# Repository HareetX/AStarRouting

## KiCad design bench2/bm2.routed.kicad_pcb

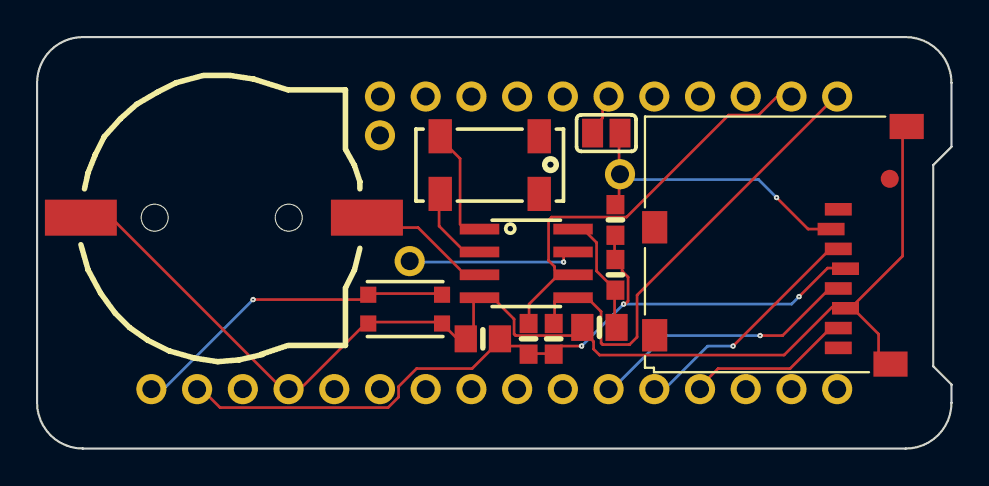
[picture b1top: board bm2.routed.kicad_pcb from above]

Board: 2 copper layers, 50.8 x 22.9 mm, 18 parts (0 on the bottom side), 15 nets.

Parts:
B1: cr1220; CR1220-2
C1, C2: 10uF; 0805-NO
FID1: FIDUCIAL_1MM
IC1: PCF8523T; SOIC8_150MIL
INT1: 1X01_ROUND
JP1: 1X11_ROUND
JP2: 1X16_ROUND
JP3: 1X01_ROUND
R1, R2: 10K; 0603-NO
R3: 100K; 0603-NO
R4: 1K; 0603-NO
SDCS: 1X01_ROUND
SJ1: SOLDERJUMPER_CLOSEDWIRE
SW1: KMR2; BTN_KMR2_4.6X2.8
X4: microsd; MICROSD
Y1: 32khz; CRYSTAL_8X3.8

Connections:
+3V3: C2.1, JP2.15, R1.2, R2.2, R3.2, R4.1, X4.4
CR1220: B1.+, IC1.3
CS: JP1.6, SJ1.1
GND: B1.-, C1.2, C2.2, IC1.4, JP2.13, SW1.A, SW1.A', X4.6, X4.MT1, X4.MT2
INT1: IC1.7, INT1.1
MISO: JP2.4, X4.7
MOSI: JP2.5, X4.3
unnamed: C1.1, IC1.8, R4.2
unnamed: IC1.1, Y1.P$4
unnamed: IC1.2, Y1.P$1
RESET: JP2.16, SW1.B, SW1.B'
SCK: JP2.6, X4.5
SCL: IC1.6, JP1.10, R2.1
SDA: IC1.5, JP1.11, R1.1
SD_CS: R3.1, SDCS.1, SJ1.2, X4.2

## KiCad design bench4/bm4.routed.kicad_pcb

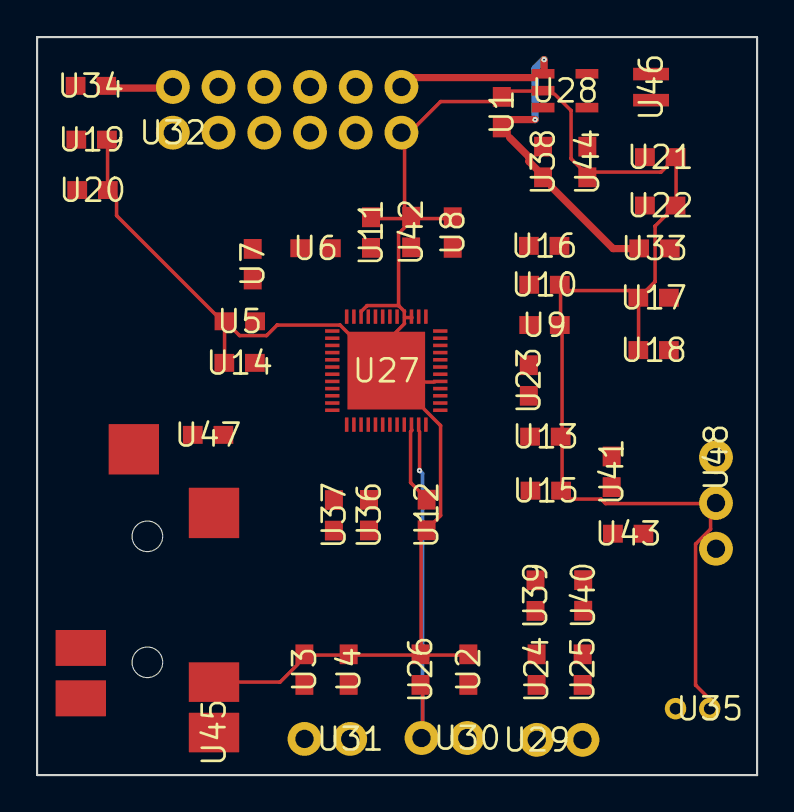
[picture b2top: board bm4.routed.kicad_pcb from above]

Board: 2 copper layers, 40.0 x 41.0 mm, 48 parts (0 on the bottom side), 47 nets.

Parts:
U1, U2, U3, U4, U5, U6, U7, U8, U9, U10, U11, U12, U13, U14, U15, U16, U17, U18, U19, U20, U21, U22, U23, U24, U25, U26, U33, U34, U36, U37, U38, U39, U40, U41, U42, U43, U44, U47: 0603
U27: QFN50P700X700X100-49N
U28: SOT95P284X122-5N
U29, U30, U31: 1X02
U32: 2X6
U35: CMC-2242PBL-A
U45: SJ-43514-SMT-TR
U46: NRH2412T2R2MNGH
U48: 1X03

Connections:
3.3V: U32.2, U34.2
5V: U1.2, U28.1, U32.12, U33.2, U38.1
/1.8VDD: U21.1, U22.1, U27.7, U27.13, U27.21, U28.4, U46.2
/3.3VDD: U19.1, U20.1, U27.29, U34.1, U36.1, U37.1, U48.1
/CPVREF: U27.17, U42.1
/HPOL: U27.18, U45.2, U47.1
/HPOR: U27.19, U45.3
/IN1P: U23.1, U27.4, U41.2, U45.1
/IN2P: U16.1, U35.2, U43.2, U48.3
/LOUTL: U27.11, U39.1
/LOUTR: U27.12, U40.1
/MICBIAS1: U15.2, U27.2, U41.1, U43.1
/SPKVDD: U17.1, U18.1, U27.44, U27.48, U33.1
/SPOLN: U26.1, U27.47, U30.2
/SPOLP: U2.1, U27.1, U30.1
/SPORN: U3.1, U27.43, U31.2
/SPORP: U4.1, U27.45, U31.1
/XADUIO_I2S0_BCLK: U27.37, U32.5
/XADUIO_I2S0_LRCKL: U27.36, U32.1
/XADUIO_SCL: U27.39, U32.7, U37.2
/XAUDIO_I2S0_DIN: U27.35, U32.4
/XAUDIO_I2S0_DOUT: U27.34, U32.3
/XAUDIO_I2S0_MCLK: U27.38, U32.6
/XAUDIO_IRQ: U27.41, U32.10
/XAUDIO_SDA: U27.40, U32.8, U36.2
GND: U1.1, U2.2, U3.2, U4.2, U5.2, U8.1, U9.1, U10.1, U11.2, U12.1, U13.1, U14.1, U15.1, U17.2, U18.2, U19.2, U20.2, U21.2, U22.2, U26.2, U27.5, U27.15, U27.16, U27.22, U27.49, U28.2, U32.11, U35.1, U42.2, U44.1, U45.4, U48.2
unnamed: U11.1, U27.20
unnamed: U23.2, U27.6
unnamed: U24.1, U39.2
unnamed: U24.2, U29.1
unnamed: U25.1, U40.2
unnamed: U25.2, U29.2
unnamed: U5.1, U27.27
unnamed: U6.1, U27.24
unnamed: U6.2, U27.23
unnamed: U7.1, U27.25
unnamed: U7.2, U27.26
unnamed: U8.2, U27.14
unnamed: U9.2, U27.8
unnamed: U10.2, U27.9
unnamed: U12.2, U27.46
unnamed: U13.2, U27.3
unnamed: U14.2, U27.28
unnamed: U16.2, U27.10
unnamed: U28.3, U38.2, U44.2
unnamed: U28.5, U46.1
unnamed: U45.5, U47.2

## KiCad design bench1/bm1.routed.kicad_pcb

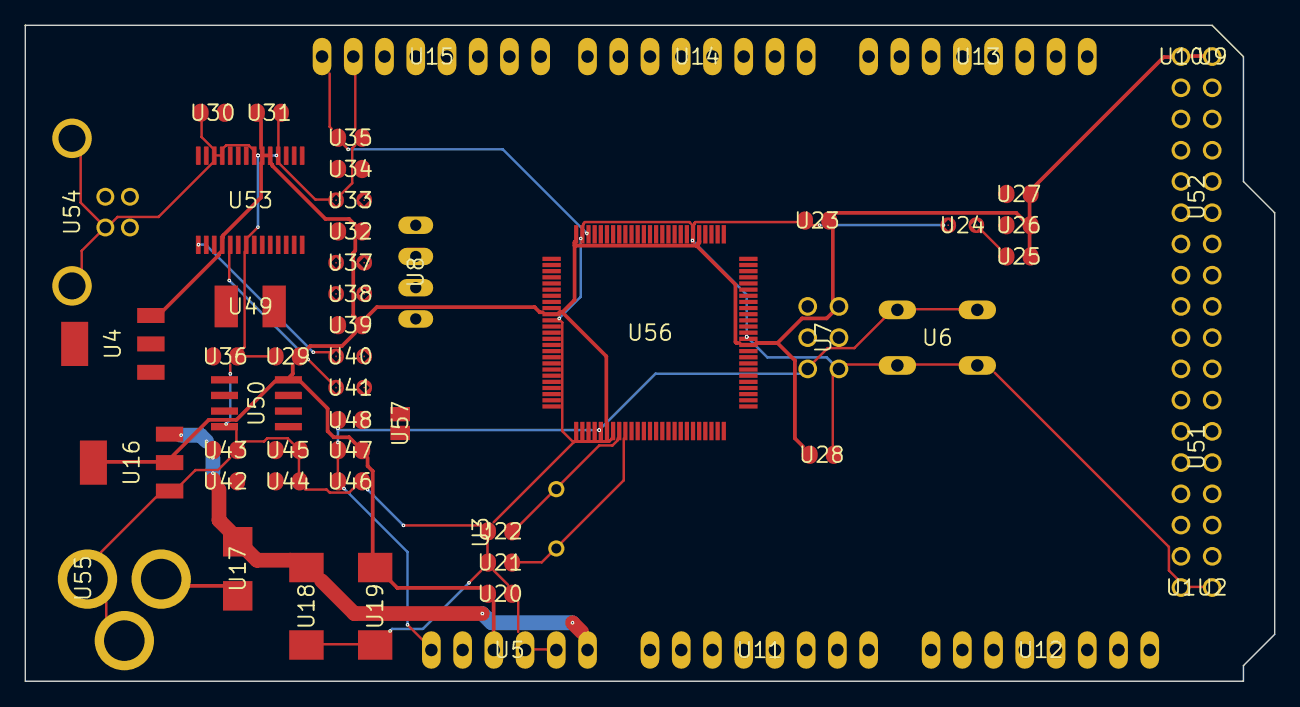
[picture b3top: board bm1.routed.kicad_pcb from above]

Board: 2 copper layers, 101.6 x 53.3 mm, 57 parts (0 on the bottom side), 99 nets.

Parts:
U1, U2, U9, U10: 1X01
U3: HC49_S
U4, U16: SOT223
U5: 1X06
U6: B3F-10XX
U7: 2X03
U8: JP4
U11, U12, U13, U14, U15: 1X08
U17: SMB
U18, U19: SMC_D
U20, U21, U22, U23, U28, U29, U30, U31, U35, U36, U43, U44, U46, U48: C0805RND
U24, U33, U37, U38: 0805RND
U25, U26, U27, U32, U34, U39, U42, U45, U47: R0805RND
U40, U41: RCL_0805RND
U49: L1812
U50: SO08
U51, U52: 2X08
U53: SSOP28
U54: PN61729
U55: DC-21MM
U56: TQFP100
U57: SJ

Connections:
+3V3: U5.2, U30.2, U50.2, U53.17
+5V: U4.3, U5.3, U7.2, U9.1, U10.1, U16.2, U16.4, U19.+, U20.1, U23.1, U25.1, U26.1, U27.1, U28.1, U29.2, U31.1, U32.2, U39.2, U47.2, U50.8, U53.4, U53.19, U53.20, U56.10, U56.31, U56.61, U56.80, U56.100
ADC0: U11.1, U56.97
ADC1: U11.2, U56.96
ADC2: U11.3, U56.95
ADC3: U11.4, U56.94
ADC4: U11.5, U56.93
ADC5: U11.6, U56.92
ADC6: U11.7, U56.91
ADC7: U11.8, U56.90
ADC8: U12.1, U56.89
ADC9: U12.2, U56.88
ADC10: U12.3, U56.87
ADC11: U12.4, U56.86
ADC12: U12.5, U56.85
ADC13: U12.6, U56.84
ADC14: U12.7, U56.83
ADC15: U12.8, U56.82
AREF: U15.8, U35.1, U56.98
CMP: U42.1, U44.2, U45.2, U50.3
CTS: U8.1, U53.11
D+: U53.15, U54.3
D-: U53.16, U54.2
DCD: U8.3, U53.10
DSR: U8.2, U53.9
DTR: U48.1, U53.2, U57.1, U57.2
GATE_CMD: U4.1, U50.6, U50.7
GND: U1.1, U2.1, U5.4, U5.5, U6.1, U6.2, U7.6, U15.7, U16.1, U18.-, U19.-, U20.2, U21.1, U22.1, U23.2, U24.P$2, U28.2, U29.1, U30.1, U31.2, U33.P$2, U35.2, U36.2, U43.2, U44.1, U45.1, U46.2, U50.4, U53.7, U53.18, U53.21, U53.25, U53.26, U54.4, U54.P$1, U54.P$2, U55.1, U55.3, U56.11, U56.32, U56.62, U56.81, U56.99
M8RXD: U40.P$1, U53.1
M8TXD: U41.P$1, U53.5
unnamed: U33.P$1, U34.2
unnamed: U24.P$1, U25.2
unnamed: U50.1, U50.5
unnamed: U3.1, U21.2, U56.34
unnamed: U3.2, U22.2, U56.33
unnamed: U38.P$2, U53.23
unnamed: U37.P$2, U53.22
unnamed: U32.1, U38.P$1
unnamed: U37.P$1, U39.1
unnamed: U49.2, U54.1
PA0: U52.16, U56.78
PA1: U52.15, U56.77
PA2: U52.14, U56.76
PA3: U52.13, U56.75
PA4: U52.12, U56.74
PA5: U52.11, U56.73
PA6: U52.10, U56.72
PA7: U52.9, U56.71
PB0: U51.1, U56.19
PB1: U7.3, U51.2, U56.20
PB2: U7.4, U51.3, U56.21
PB3: U7.1, U51.4, U56.22
PB4: U15.3, U56.23
PB5: U15.4, U56.24
PB6: U15.5, U56.25
PB7: U15.6, U34.1, U56.26
PC0: U52.1, U56.53
PC1: U52.2, U56.54
PC2: U52.3, U56.55
PC3: U52.4, U56.56
PC4: U52.5, U56.57
PC5: U52.6, U56.58
PC6: U52.7, U56.59
PC7: U52.8, U56.60
PD7: U51.16, U56.50
PE0: U14.1, U40.P$2, U56.2
PE1: U14.2, U41.P$2, U56.3
PE3: U14.6, U56.5
PE4: U14.3, U56.6
PE5: U14.4, U56.7
PG0: U51.13, U56.51
PG1: U51.14, U56.52
PG2: U51.15, U56.70
PG5: U14.5, U56.1
PH3: U14.7, U56.15
PH4: U14.8, U56.16
PH5: U15.1, U56.17
PH6: U15.2, U56.18
PL0: U51.5, U56.35
PL1: U51.6, U56.36
PL2: U51.7, U56.37
PL3: U51.8, U56.38
PL4: U51.9, U56.39
PL5: U51.10, U56.40
PL6: U51.11, U56.41
PL7: U51.12, U56.42
PWRIN: U17.A, U55.2
RESET: U5.1, U6.3, U6.4, U7.5, U46.1, U47.1, U48.2, U56.30
RI: U8.4, U53.6
RXD1: U13.3, U56.45
RXD2: U13.5, U56.12
RXD3: U13.7, U56.63
SCL: U13.1, U26.2, U56.43
SDA: U13.2, U27.2, U56.44
TXD1: U13.4, U56.46
TXD2: U13.6, U56.13
TXD3: U13.8, U56.64
USBVCC: U4.2, U36.1, U49.1
VIN: U5.6, U16.3, U17.C, U18.+, U42.2, U43.1

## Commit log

2023-05-31 finish AStarSolver.py
2023-05-31 merge_route is not finish
2023-06-04 plot in TKAgg
2023-06-07 fix plot bug
2023-06-09 finish grid_graph: ndarray, but there is something wrong.
2023-06-11 fix the bug in grid_graph: ndarray.
2023-06-14 add trace option
2023-06-15 update env_msg when a multi-net is routed
2023-06-24 add kicad_pro parser
2023-06-27 prepare to change obstacles logic
2023-06-29 prepare to change obstacles logic v1
2023-06-30 has changed obstacles logic v1
2023-07-03 prepare to add pad shape
2023-07-08 optimized via cost
2023-07-10 add comment and delete the grid graph data structure
